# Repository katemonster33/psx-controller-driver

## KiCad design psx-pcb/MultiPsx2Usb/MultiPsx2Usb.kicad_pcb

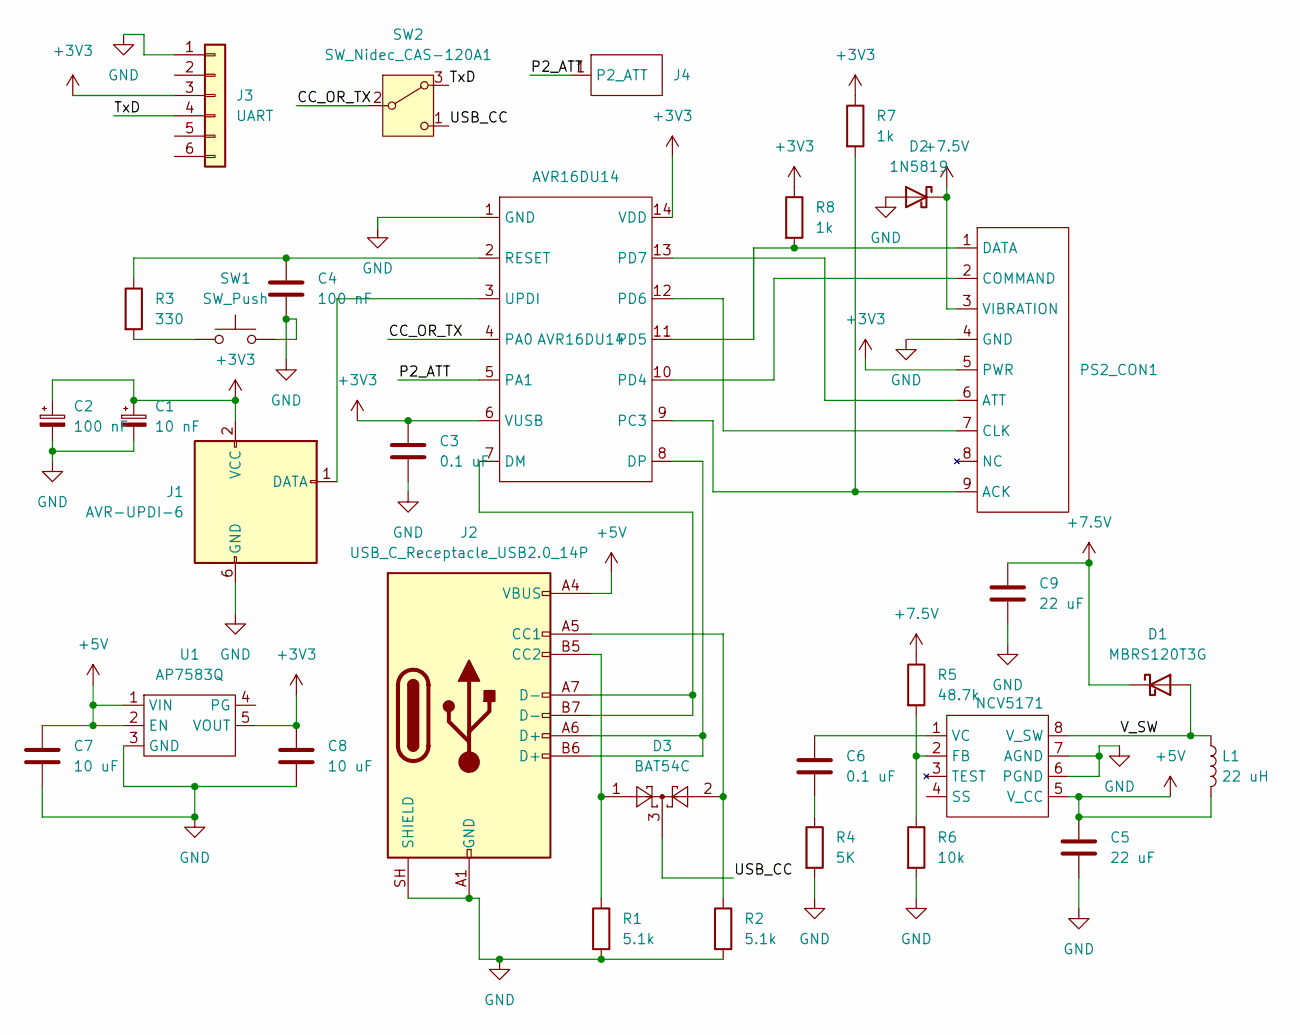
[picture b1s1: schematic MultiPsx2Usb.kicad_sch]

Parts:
AVR16DU14: AVR16DU14; SOIC-14
C1: 10 nF; C_0603_1608Metric_Pad1.08x0.95mm_HandSolder
C2, C4: 100 nF; C_0603_1608Metric_Pad1.08x0.95mm_HandSolder
C3, C6: 0.1 uF; C_0603_1608Metric_Pad1.08x0.95mm_HandSolder
C5, C9: 22 uF; C_0603_1608Metric_Pad1.08x0.95mm_HandSolder
C7, C8: 10 uF; C_0603_1608Metric_Pad1.08x0.95mm_HandSolder
D1: MBRS120T3G; D_SMB_Handsoldering
D2: 1N5819; D_SOD-123
D3: BAT54C; SOT-23
J1: AVR-UPDI-6; PinHeader_2x03_P2.54mm_Vertical
J2: USB_C_Receptacle_USB2.0_14P; USB_C_Receptacle_GCT_USB4105-xx-A_16P_TopMnt_Horizontal
J3: UART; PinHeader_1x06_P2.54mm_Vertical
J4: PS2_P2
L1: 22 uH; L_Bourns_SRN6045TA
NCV5171: SOIC-8-1EP_3.9x4.9mm_P1.27mm_EP2.41x3.81mm_ThermalVias
PS2_CON1: PS2_CONNECTOR
R1, R2: 5.1k; R_0603_1608Metric_Pad0.98x0.95mm_HandSolder
R3: 330; R_0603_1608Metric_Pad0.98x0.95mm_HandSolder
R4: 5K; R_0603_1608Metric_Pad0.98x0.95mm_HandSolder
R5: 48.7k; R_0603_1608Metric_Pad0.98x0.95mm_HandSolder
R6: 10k; R_0603_1608Metric_Pad0.98x0.95mm_HandSolder
R7, R8: 1k; R_0603_1608Metric_Pad0.98x0.95mm_HandSolder
SW1: SW_Push; SW_Push_1P1T_XKB_TS-1187A
SW2: SW_Nidec_CAS-120A1; Nidec_Copal_CAS-120A
U1: AP7583Q; TO-252-5_TabPin3

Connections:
+3V3: AVR16DU14.6 (VUSB), AVR16DU14.14 (VDD), C1.1, C2.1, C3.1, C8.1, J1.2 (VCC), J3.3, PS2_CON1.5 (PWR), R7.1, R8.1, U1.5 (VOUT)
+5V: C5.1, C7.1, J2.A4 (VBUS), J2.A9 (VBUS), J2.B4 (VBUS), J2.B9 (VBUS), L1.2, NCV5171.5 (V_CC), U1.1 (VIN), U1.2 (EN)
+7.5V: C9.1, D1.1 (K), D2.1 (K), PS2_CON1.3 (VIBRATION), R5.1
/<NO NET>: AVR16DU14.4 (PA0), SW2.2 (B)
/P2_ATT: AVR16DU14.5 (PA1), J4.1 (P2_ATT_1)
/TxD: J3.4, SW2.3 (A)
/USB_CC: D3.3, SW2.1 (C)
/V_SW: D1.2 (A), L1.1, NCV5171.8 (V_SW)
GND: AVR16DU14.1 (GND), C1.2, C2.2, C3.2, C4.2, C5.2, C7.2, C8.2, C9.2, D2.2 (A), J1.6 (GND), J2.A1 (GND), J2.A12 (GND), J2.B1 (GND), J2.B12 (GND), J2.SH (SHIELD), J3.1, NCV5171.6 (PGND), NCV5171.7 (AGND), PS2_CON1.4 (GND), R1.2, R2.2, R4.2, R6.2, SW1.2, U1.3 (GND)
unnamed: AVR16DU14.7 (DM), J2.A7 (D-), J2.B7 (D-)
unnamed: AVR16DU14.8 (DP), J2.A6 (D+), J2.B6 (D+)
unnamed: AVR16DU14.9 (PC3), PS2_CON1.9 (ACK), R7.2
unnamed: AVR16DU14.10 (PD4), PS2_CON1.2 (COMMAND)
unnamed: AVR16DU14.11 (PD5), PS2_CON1.1 (DATA), R8.2
unnamed: AVR16DU14.12 (PD6), PS2_CON1.7 (CLK)
unnamed: AVR16DU14.13 (PD7), PS2_CON1.6 (ATT)
unnamed: AVR16DU14.2 (RESET), C4.1, R3.1
unnamed: AVR16DU14.3 (UPDI), J1.1 (DATA)
unnamed: C6.2, R4.1
unnamed: D3.2, J2.A5 (CC1), R2.1
unnamed: D3.1, J2.B5 (CC2), R1.1
unnamed: NCV5171.2 (FB), R5.2, R6.1
unnamed: C6.1, NCV5171.1 (VC)
unnamed: R3.2, SW1.1

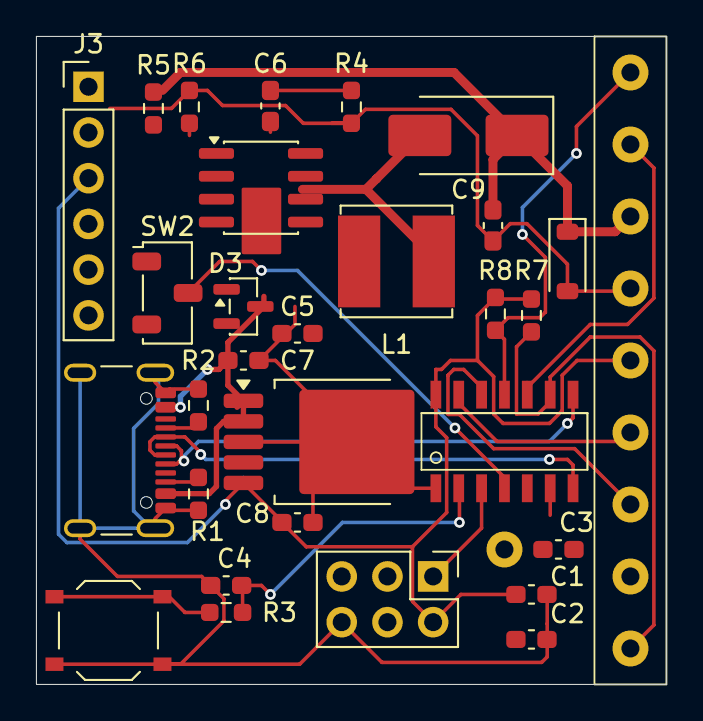
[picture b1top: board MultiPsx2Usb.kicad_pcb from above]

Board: 2 copper layers, 35.0 x 36.0 mm, 31 parts (0 on the bottom side), 24 nets.

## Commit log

2017-03-07 adding initial files
2017-03-08 Temporarily committing to ensure changes not lost.
2017-03-08 cleaning out bad commit of linux project
2017-03-08 committing actual CPP files for kdevelop
2017-03-08 Rewrote large parts of Arduino code to be more broadcast-based. This way, arduino can continuously monitor the controller, and only notify the client when bits change
2017-03-10 Resolved random inputs. Changed bus speed to 250khz.
2017-03-10 Added rumble. Setting analog mode on automatically during connection. Seems to not disturb PSX controllers, but various problems happen on those. Will deal with them shortly.
2017-03-15 Made small timing tweaks to ensure compatibility with DualShock 1. Tested with digital controller. Still some strange issues when analog and digital controller are plugged in together. Rumble functio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
2017-03-17 updated to work with the new broadcast-based Arduino code
2017-07-20 PS2 Controller Driver - Arduino to PC (Linux)
    This is a driver which uses an Arduino to translate the inputs from a PS2 controller to serial data, and on the Linux side, translates the inputs to joysticks. When the user plugs a controller into t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
2019-05-28 made whitespace changes because i felt like it.
2022-06-04 Committing psxpi.c
    SPI-based driver for communicating with a PSX/PS2 controller via Raspberry Pi
2022-06-04 Committing fork of spi-bcm2835.c
    Committing special version of spi-bcm2835 that is keyed to include the "ACK" line support for communicating with PSX/PS2 controllers and peripherals.
2022-06-04 Rename pspi-raspberrypi to pspi-kernel-driver/spi-bcm2835.c
2022-06-04 Committing fork of spi-bcm2835aux.c
    Forking spi-bcm2835.c to add support for an ACK line for PSX/PS2 controllers and peripherals
2022-06-07 Adding GPIO support to main SPI driver
2022-06-09 small edits
2022-07-28 Added Makefile, renamed file to avoid collisions with existing SPI module, added PSX to name to specify new usage
2026-05-06 Moved the arduino code to using SPI for communication
2026-05-10 Adding initial commit for PCB (just symbol/footprint for AVR32DU for now)
2026-05-13 Committing latest changes to schematic
2026-05-14 Rough schematic mockup done. need to create test circuits and see what works and what doesn't.
2026-05-14 latest schematic changes. added MPLAB X project for code for the AVR16DU PCB, ported code from Arduino, added USB support
2026-05-16 Populated PCB, finished adding everything I should need
2026-05-22 worked on changes to make code compile. tweaking the CPU speed to allow for the SPI clock divider to give us even 250 kHz, 500 kHz, and 1 MHz speeds.
2026-05-22 Finished designing the PCB, track widths have been set for all net classes, still need to fix GND track width
2026-05-22 port muxing changes, hopefully SPI is routed correctly now
2026-05-22 more tweaks to match the actual port layout of the AVR16DU14. still need to tweak USB
2026-05-22 Fixed remaining compilation issues with USB stuff, hopefully the commented-out lines are not needed, could not find any source in data sheet for what the code was trying to do.
2026-05-25 Deleted the USB code, used MPLAB Code Configurator to auto-generate a USB stack for a generic HID device. Code works so I've done the minimum effort to port the SPI code over. Probably doesn't work a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
2026-05-25 missed some config file and a random assembly file for git. updated .gitignore to weed out the IDE-generated files
2026-05-25 one more file extension
2026-05-25 GND track width increased to 20 mils to match +7.5V, still need to update PCB
2026-05-25 working on restoring functionality, adding back ACK detection
2026-05-26 fixed configuration issues causing controller to not communicate. tested and working
2026-05-27 Expose four HID gamepads over USB
2026-05-27 Support dynamic HID gamepad reenumeration and 11-button mapping
2026-06-12 fixed inductor footprint. added 6-pin FTDI header. connected V_USB to 3.3V instead of 5V.
2026-06-12 Added USART0. trying to add example code to make it work. need to redesign board to get it done.
2026-06-12 added old csv files where i logged the SPI message communication between PSX and multitap.
2026-06-24 Added circuitry to allow for serial TX, which is switchable with a microswitch to USB CC pin voltage measurement. Added player 2 ATT pin support
